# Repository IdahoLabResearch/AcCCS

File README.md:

# AcCCS
Access Capabilities for CCS (AcCCS - pronounced "access" /ˈakˌses/) provides a flexible and inexpensive solution to enable communications testing of various Electric Vehicle (EV) technologies that use the CCS charging standard(s).  This codebase is an example of tools and scripts capable of communicating with and emulating an Electric Vehicle Communications Controller (EVCC) and/or a Supply Equipment Communications Controller (SECC).

This project is the result of our efforts to find COTS hardware and existing open source software capable of communicating via HomePlug GreenPHY (HPGP) with CCS enabled vehicles and charging stations.  We are providing some basic scripts to emulate an EV (see [run_evcc.py](run_evcc.py)) or an EVSE (see [run_secc.py](run_secc.py)).  These two scripts utilize a third-party open source project that provide Scapy packet definitions for Layer 2 (HPGP - [layerscapy](https://github.com/FlUxIuS/HomePlugPWN/tree/master/layerscapy)). Our goal was to establish a persistent network connection with a target device so that we can test the device for network vulnerabilities.

To enable some testing of the IPv6 endpoints, the emulator scripts provide the ability to perform some basic port scans of the target.  This functionality is available using command-line options of the emulator.  The emulators can be further enhanced for additional port scanning activities or even fuzz testing of the selected CCS protocol.

> **Note:** This code was primarily developed and tested using the old DIN 70121 specification and schema.

A description of the [CurrentImplementation](/docs/CurrentImplementation.md) of our AcCCS box, as well as some supporting presentations, are found in the [docs](/docs/) folder.

**A final word:** All of this code was generated in our lab using extensive trial and error while monitoring communications between a couple EV and EVSE.  It has not been extensively tested with many vehicles or charging stations.  It was not written using formal software development and design methods.  We were just happy when it worked.  It is not pretty.

## Getting Started

For the full fresh-clone walkthrough — submodule clone, Python dependencies,
PKI certificates, the virtual veth pair, and a smoke test — see
[Project Setup](#project-setup).

## Hardware Configuration

Details regarding our current implementation and hardware configuration is found in the '''docs''' folder.

The ```resources``` directory includes the schematics and design files to create the PWM board used to emulate the SECC.  The following shows how all of the hardware is currently setup in the AcCCS boxes.

EVSE DEVOLO: [EVSE side configured dLAN Green Phy Eval Board](https://www.codico.com/en/evse-side-configured-dlan-green-phy-eval-board)\
PEV DEVOLO: [PEV side configured dLAN Green Phy Eval Board](https://www.codico.com/en/pev-side-configured-dlan-green-phy-eval-board)\
RASPBERRY PI: [Raspberry Pi 4 Model B](https://www.raspberrypi.com/products/raspberry-pi-4-model-b/)\
12V OUT: [12V Isolated DC/DC Converter](https://www.digikey.com/en/products/detail/cui-inc./PYBE30-Q24-S12-T/9859982)\
5V OUT: [5V Isolated DC/DC Converter](https://www.digikey.com/en/products/detail/cui-inc/PYBE30-Q24-S5-T/9859981)\
ETH: [USB to RJ45 Adapter](https://www.amazon.com/Gigabit-Adapter-CableCreation-Network-Supporting/dp/B07CKQY8HN)\
PWM PCB: [PWM PCB](resources/PWM_PCB/)

The devices labeled ETH, RELAY, 5V OUT, 12V OUT, and RASPBERRY PI are generic devices so a specific brand is not required. Nevertheless, the above links provided are the exact version of these devices we used in our AcCCS box. A brief description of each of these devices are as follows so that any devices that fits this description can probably be used with little to no alteration. Extra notes regarding the implementation and role of each device are also included.

**RASPBERRY PI:** For this project a raspberry pi was used, but any computer or microcontroller can be used in its place. A pi was used for its small form factor, I2C interface, and ability to run an OS. Whatever device is used for this role must support the following features: IPv4 and IPv6 networking, I2C interface (PWM board), 3 RJ-45 ports or the ability to connect RJ-45 adapters, and python support (unless you don't want to use the scripts provided in this project).

**PWM PCB and RELAYS:** The PWM circuit includes several on-board relays. The first two channels of the relay are used to emulate the J1772 states of a PEV. The J1772 signaling circuit below shows the resistance values used (found in the vehicle controller portion labeled R3 and R2). The next 2 channels are used to connect and disconnect the control pilot and proximity pilot lines for the EVSE emulation to mimic plugging and unplugging the charging cable. When connected, the control pilot line goes directly to the output and the proximity pilot ties a resistance to ground in accordance to the J1772 standard (R6 in the EVSE connector of the signaling circuit).

**12V/5V OUT:** These DC/DC power converters were used as a means to get +12V,-12V, and +5V power supplies, so they are not necessary if you have a way to supply these voltages by other means. If the provided configuration is used, the converters must be **ISOLATED** DC/DC converters so that you can tie the positive terminal of one 12V supply to the negative terminal of the other in order to create a -12V supply.

**ETH:** Any generic USB to RJ-45 adapter can be used. This is needed so that the Raspberry pi can interface with the two GreenPHY eval board radios via ethernet. Not necessary if your choice of controller has 3 RJ-45 ports.

**EVSE/PEV DEVOLO:** The GreenPHY eval board used acts as a radio that bridges ethernet communications over cat cable to HomePlug GreenPHY communications over a single signal wire and ground. These boards also automatically complete some of the level 2 HomePlug protocol specific actions, such as forming ALVNs according to the standard, so to work properly must be configured properly. Currently, these radios are purchased pre-configured from the vendor, but there may be some way to flash an unconfigured board with the contents of a configured board. There are also some jumper options present on the eval boards which should be configured so that the HomePlug GreenPHY is output over the two-wire terminal instead of coax.

The circuit shown below is what is used to generate the +12V to -12V 1kHz 5% Duty Cycle PWM signal that is supplied by the EVSE controller. It uses the TLC555CP chip to first generate a +12V to 0V 1kHz 5% Duty Cycle PWM. Other timer ICs could probably be used, but this is what worked for me. The output PWM's frequency and duty cycle are dependant on the values of two resistors and one capacitor (the 1.5k and 25k Ohm resistors and the 47 nanoFarad capacitor). In practice, the values of these components varied enough for the resulting signal to not fit within tolerances for the EVCC to recognize it as a 1kHz 5% PWM. So, in place of a 1.5k resistance a 10k potentiometer was used and in place of a 25k resistance a 22k resistor in series with a 10k potentiometer was used. In this configuration, the output of the 555 timer was probed with an oscilloscope and the potentiometers were tuned until the PWM was as close to the spec as possible. Next, the signal along with -12V DC is input into an Op-Amp so that the resulting output will be the required +12V to -12V PWM. In practice, the resulting PWM is closer to an +11V peak than +12V, so to compensate the resistor in series with the output was changed to a lower value (from a 1k Ohm to a 680 Ohm resistor). This is done so that when the PEV changes its internal resistances and changes the J1772 states, the resulting voltages are closer to the +9V and +6V peaks required by the standard.

555 Timer: [TLC555CP](https://www.digikey.com/en/products/detail/texas-instruments/TLC555CP/277502)\
Op-Amp: [LM6132BIN/NOPB](https://www.ti.com/product/LM6132/part-details/LM6132BIN/NOPB)

## Software Configuration

The DIN and ISO standards define that the TCP/IP communication between EVCC and SECC equipment use IPv6 networking with link-local addressing. For this reason, to properly communicate to these devices from a controller, IPv6 networking on the controller must be configured for link-local addressing on the interfaces that connect to the GreenPHY eval board radios.

### Python Module Dependencies
* scapy
* smbus
* expy

**Scapy** is used for all of the packet activities such as crafting, manipulation, sending, and receiving packets. 

**Smbus** is used for I2C communications with the PCB to operate the relays found on the PWM PCB.

**EXPy** is the Python binding over LF Energy EVerest's `libcbv2g` used for EXI
encode/decode (see [ADR-0002](docs/adr/0002-expy-codec-replacement.md)). EXPy is
installed from source and builds a C/C++ extension during `pip install`, which
adds the following install-time prerequisites on every target (dev machine and
Raspberry Pi alike):

* **CMake** ≥ 3.20
* **Ninja** ≥ 1.10
* A C/C++ toolchain (gcc/clang and the matching standard libraries)

Install these *before* `pip install` — [Project Setup](#project-setup) step 2
covers the Debian / Raspberry Pi OS one-liner.

### EVSE and EV Python Scripts
Below is a brief description of the entry-point scripts in this project. These scripts are provided as examples of how you might utilize this hardware in your own testing environment. This is not intended to be a finished product with all desired functionality. Some functionality is still a work in progress.

**run_secc.py:** Emulates an EVSE (SECC). When the AcCCS's EVSE CP and SIG GND are connected to the PEV's CP and GND, the script follows the J1772 spec by going through layer 2 HomePlug GreenPHY SLAC negotiations, layer 3 UDP SECC Discovery Protocol, and then layer 3 TCP/IPv6 communications. DIN SPEC 70121, ISO 15118-2, and ISO 15118-20 (AC and DC) are all supported, including TLS sessions, Plug & Charge, and bidirectional power transfer; which one a run speaks is chosen by the personality's `capabilities.supported_protocols` (see [Running the emulators](#running-the-emulators)).

**run_evcc.py:** Same as run_secc.py but for the EV side (EVCC); AcCCS's PEV CP and SIG GND should be connected to the EVSE's CP and GND pins.

A man-in-the-middle mode — two simultaneous connections to a PEV and an EVSE with packets forwarded (and optionally modified) between them — remains unimplemented. A simple bridge between the two is not workable because of the high cross-talk between CP lines, and the signalling is very susceptible to RF interference.

### Hardware bench tools

These helper scripts drive the I2C relay board directly, without loading a personality or opening a V2G session. They run only on the hardware host (the Pi, with the relay board on I2C bus 1); off the hardware — no `smbus`, no bus, or no permission on `/dev/i2c-1` — each exits with a one-line explanation rather than a traceback.

**scripts/evcc_relays.py:** Interactive control of the EV side's control-pilot relays for exercising the CP/PP wiring in isolation. Type a J1772 state (`a`/`b`/`c`) and watch the EVSE react; the relays are always opened again on exit. Like the emulator it touches only the EV side's pins, so a SECC running on the same box keeps its relays.

**scripts/reset_relays.py:** Turns *every* relay off in one deliberate whole-register write, regardless of which role set the bits. This recovers a board whose relays a hard-killed emulator left latched closed — the one case the per-role writes cannot clean up, since the owner is no longer around to clear them. It is the single sanctioned exception to the role-ownership rule (see [ADR-0007](docs/adr/0007-role-scoped-relay-ownership.md)); the pin-direction configuration is left untouched. **Do not run it while an emulator is live** — the same broad write that recovers an orphaned board will clear a healthy session's relays out from under it. It reports whether it cleared anything or found the board already off.

## Project Setup

This is the single, linear path from a fresh clone to a green virtual demo
session. Follow it top to bottom — each step is a prerequisite for the smoke
test at the end. The deeper reference sections below are linked from each step.

### 1. Clone with submodules

AcCCS vendors its third-party Layer 2 (HPGP) libraries as git submodules, so a
plain `git clone` is not enough:

```bash
git clone --recurse-submodules <clone-url>
cd AcCCS
git submodule sync
```

If git errors about locating specific repository versions, this usually
unsticks it:

```bash
git submodule update --force --recursive --init --remote
```

### 2. Python environment + dependencies

Use Python 3.10+ in an isolated environment — a `conda` env or a `venv` both
work. The pinned dependencies live in [`requirements.txt`](requirements.txt):

```bash
# conda
conda create -n AcCCS python=3.11 && conda activate AcCCS
# — or — venv
python -m venv .venv && source .venv/bin/activate

pip install -r requirements.txt
```

One dependency, **EXPy**, builds a C/C++ extension at install time (see
[ADR-0002](docs/adr/0002-expy-codec-replacement.md)), so a build toolchain
must be present *before* `pip install`. On Debian / Raspberry Pi OS:

```bash
sudo apt install cmake ninja-build build-essential
```

See [Software Configuration](#software-configuration) for the full dependency
rundown.

### 3. Generate PKI certificates

The stock personalities ship with TLS enabled (`tls.use_tls: true`,
`tls.enable_tls_1_3: true`), so the SECC needs a server certificate chain
before it can complete SDP/TLS. Generate it from the repo root:

```bash
bash app/shared/pki/create_certs.sh -v iso-2
```

Skipping this step is the most common first-run failure — it surfaces as
`FileNotFoundError: oemRootCACert.pem` followed by a cascading
`'TCPServer' object has no attribute 'ipv6_address_host'` traceback.

If you intend to run ISO 15118-20 scenarios, also generate the `-v iso-20`
chain:

```bash
bash app/shared/pki/create_certs.sh -v iso-20
```

See [Certificate Management](#certificate-management) for the Plug-and-Charge
context.

### 4. Create the virtual veth pair

The `--virtual` demo runs both emulators on one host over a veth pair
(`acccs_secc ↔ acccs_evcc`, with link-local addresses `fe80::1` / `fe80::2`).
Create it with:

```bash
sudo ./setup_veth.sh
```

This is also a prerequisite for the conformance tests.

### 5. Smoke test

With steps 1–4 done, run the stock SECC and EVCC in two terminals. The
emulators bind raw sockets, so they need root (`sudo`) or the `cap_net_raw`
capability.

Note the `sudo "$(which python)"` form: `sudo` resets `PATH` to its
`secure_path`, so a plain `sudo python` runs the *system* interpreter, which
lacks the dependencies you installed into the conda/venv environment from
step 2 (you'd hit `ModuleNotFoundError: No module named 'nmap'`). The
command substitution resolves to the activated environment's interpreter
*before* `sudo` runs, so the env's Python is used:

```bash
# Terminal 1
sudo "$(which python)" run_secc.py --config default-secc --virtual

# Terminal 2 (a second or two later)
sudo "$(which python)" run_evcc.py --config default-evcc --virtual
```

A clean session walks through these milestones:

```
SLAC → SDP/TLS → SessionSetup → ServiceDiscovery → PowerDelivery →
CurrentDemand loop → PowerDelivery → WeldingDetection → SessionStop
```

ending with the EVCC logging `Going to state A`. If you see that, your setup is
complete. See [Running the emulators](#running-the-emulators) for personality
and CLI-override details.

## Running the emulators

> **New here?** Complete [Project Setup](#project-setup) first — it covers the
> submodule clone, dependencies, PKI certificates, and the veth pair that the
> commands below assume are already in place.

Only two scripts are expected to be run from command line: ```run_evcc.py``` and ```run_secc.py```. The other scripts and files serve as tools and utilities for these scripts to run.

Both scripts take an optional `--config <personality.yaml>` flag and an
optional `--runtime <runtime.yaml>`. When `--config` is omitted, each
script defaults to its per-role DIN device file (`run_secc.py` →
`din_dc_extended-secc`, `run_evcc.py` → `din_dc_extended-evcc`). Stock personalities live in the
[`personalities/`](personalities/) directory; the bundled defaults are a
complete materialised dump of every field with its built-in value:

The emulators bind raw sockets, so they need root (`sudo`) or the
`cap_net_raw` capability. Use the `sudo "$(which python)"` form so the
activated environment's interpreter is used — a plain `sudo python` resets
`PATH` to `secure_path` and runs the *system* interpreter, which lacks your
installed dependencies (see [Project Setup → Smoke test](#5-smoke-test) for
the full explanation):

```bash
# Run the stock virtual SECC and EVCC over the acccs_secc/acccs_evcc veth pair
sudo ./setup_veth.sh
sudo "$(which python)" run_secc.py --config default-secc --virtual
sudo "$(which python)" run_evcc.py --config default-evcc --virtual
```

Personality search order (per [ADR-0001](docs/adr/0001-personality-yaml-config.md)):

1. explicit `--config <path>` (file path);
2. `personalities/<name>.yaml` in the repo;
3. `~/.acccs/personalities/<name>.yaml` (user-local).

### CLI overrides

Personality fields are **not** CLI-overridable — they describe *who* the
emulated device is, and changing them mid-experiment is a different
personality. Operational knobs are overridable:

| Flag | Overrides |
|---|---|
| `--log-level <LEVEL>` | `runtime.log.console_level` |
| `--file-log-level <LEVEL>` | `runtime.log.file_level` |
| `--virtual` | `runtime.virtual` |
| `--nmap` | `runtime.nmap.enabled` |
| `--nmap-args <ARGS>` | `runtime.nmap.args` |
| `--nmap-ports <SPEC>` | `runtime.nmap.ports` |
| `--source-port <PORT>` | `runtime.source_port` |
| `--modified-cordset` | `runtime.modified_cordset` (SECC only) |

To customise a personality, copy `personalities/default-<role>.yaml` to a
new file and edit. The Pydantic loader validates strictly — unknown keys
are a hard error. See [`docs/personality-authoring.md`](docs/personality-authoring.md)
for a section-by-section authoring guide and the bundled example library.

## Certificate Management

Basic TLS certificate generation for the demo is covered in
[Project Setup](#project-setup) step 3. This section provides the deeper
Plug-and-Charge context and the contract-certificate workflow.

### Plug and Charge (ISO 15118-2 and ISO 15118-20)
For Plug and Charge, certificates and private keys have to be created at the beginning. Go to the [pki](/app/shared/pki) directory and run the ```create_certs.sh``` script like this:
```bash
./create_certs.sh -v iso-2
```
or
```bash
./create_certs.sh -v iso-20
```
If you are running it for the first time, you may have to change the permission to be able to exceute it. In this case, do this:
```bash
chmod 755 create_certs.sh
```

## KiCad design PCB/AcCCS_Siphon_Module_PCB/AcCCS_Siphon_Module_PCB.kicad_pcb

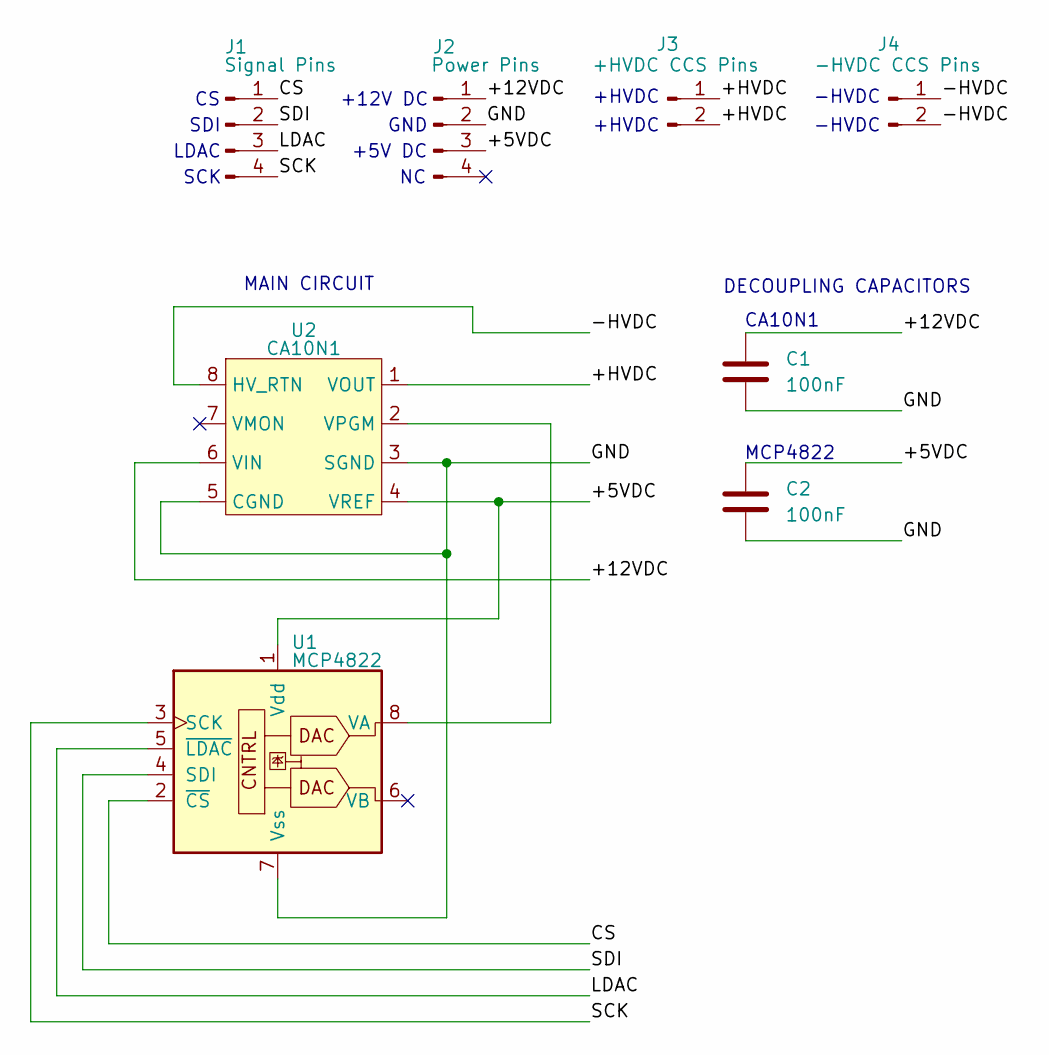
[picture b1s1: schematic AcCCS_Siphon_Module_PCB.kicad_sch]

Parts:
C1, C2: 100nF; C_Disc_D7.5mm_W5.0mm_P5.00mm
J1: Signal Pins; PinSocket_1x04_P2.54mm_Vertical
J2: Power Pins; PinSocket_1x04_P2.54mm_Vertical
J3: +HVDC CCS Pins; TerminalBlock_Phoenix_MKDS-1,5-2_1x02_P5.00mm_Horizontal
J4: -HVDC CCS Pins; TerminalBlock_Phoenix_MKDS-1,5-2_1x02_P5.00mm_Horizontal
U1: MCP4822; DIP-8_W7.62mm
U2: CA10N1; CA10N

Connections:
/+5VDC: C2.1, J2.3, U1.1 (Vdd), U2.4 (VREF)
/+12VDC: C1.1, J2.1, U2.6 (VIN)
/+HVDC: J3.1, J3.2, U2.1 (VOUT)
/-HVDC: J4.1, J4.2, U2.8 (HV_RTN)
/CS: J1.1, U1.2 (~CS)
/GND: C1.2, C2.2, J2.2, U1.7 (Vss), U2.3 (SGND), U2.5 (CGND)
/LDAC: J1.3, U1.5 (~LDAC)
/SCK: J1.4, U1.3 (SCK)
/SDI: J1.2, U1.4 (SDI)
unnamed: U1.8 (VA), U2.2 (VPGM)

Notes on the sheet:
+5V DC
MAIN CIRCUIT
+12V DC
-HVDC
+HVDC
DECOUPLING CAPACITORS
SCK
LDAC
GND
MCP4822
CA10N1
SDI

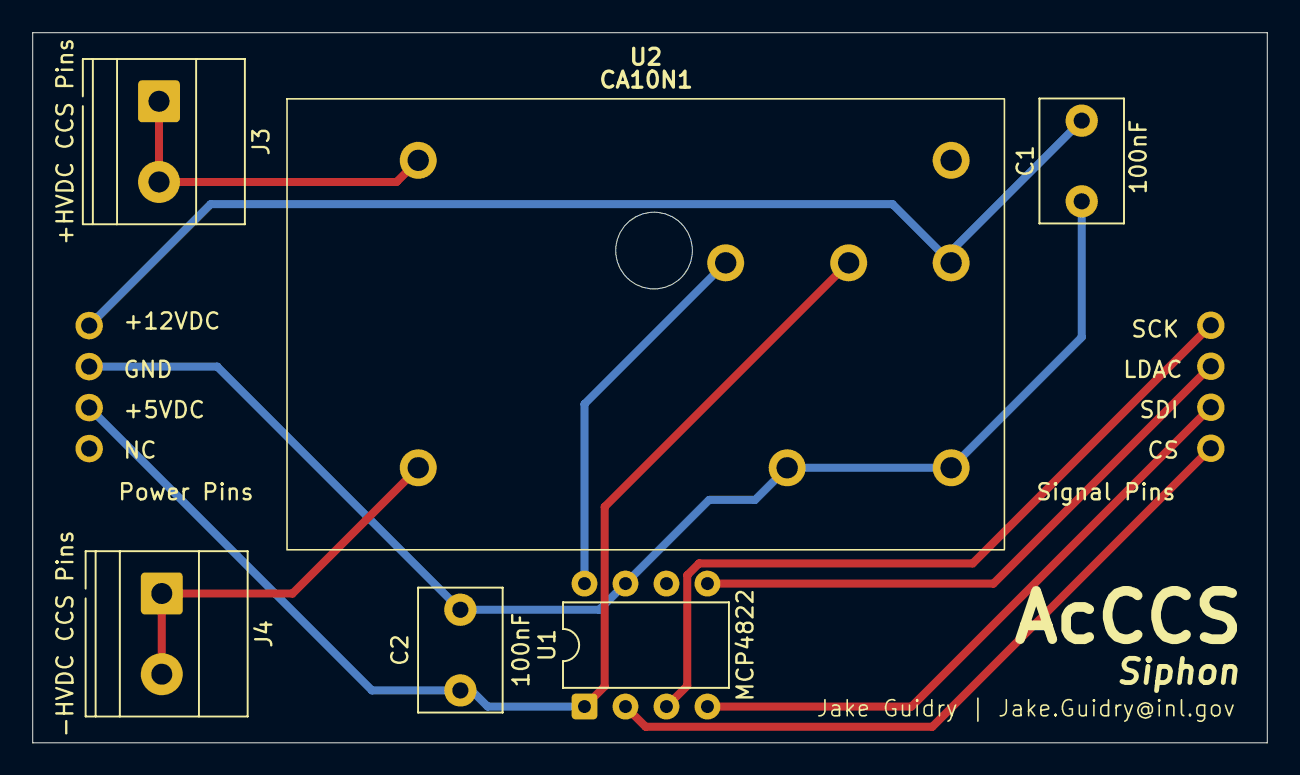
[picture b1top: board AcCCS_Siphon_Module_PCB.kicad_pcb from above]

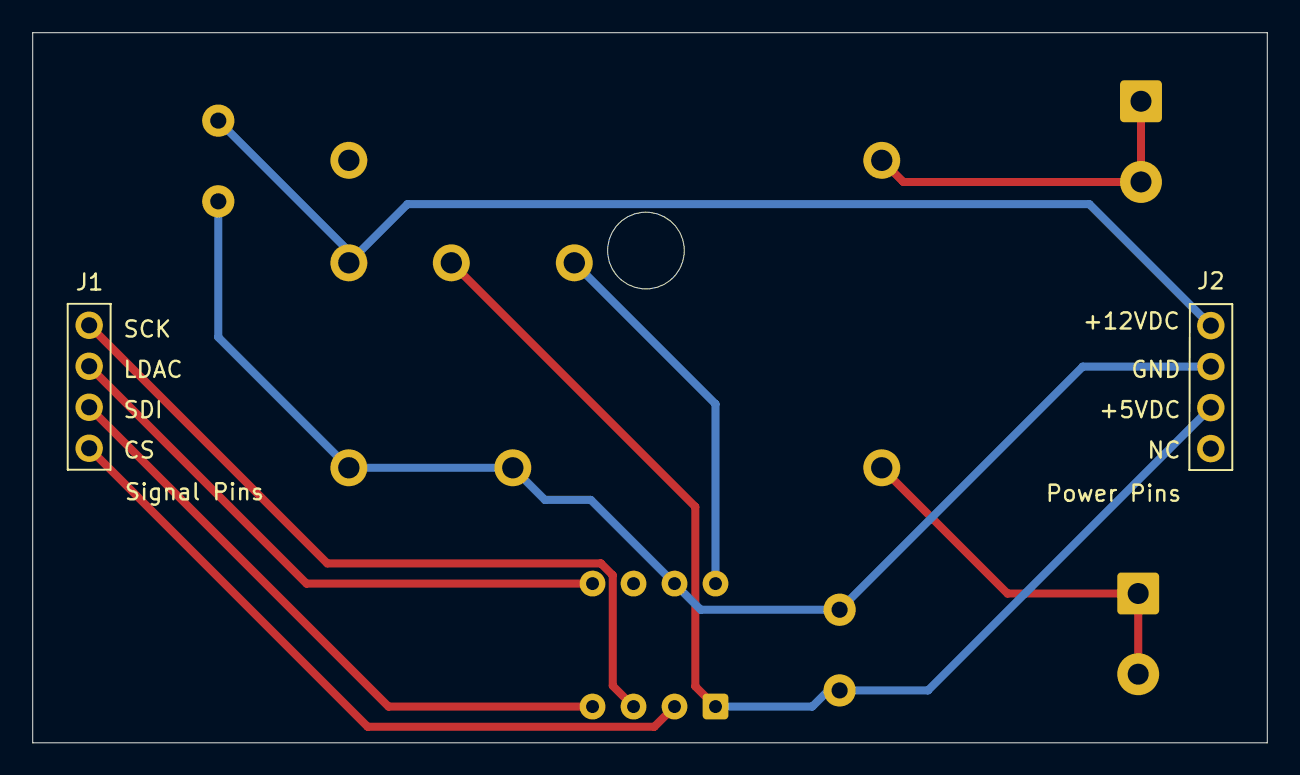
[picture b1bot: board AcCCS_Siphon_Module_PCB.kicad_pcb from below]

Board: 2 copper layers, 76.5 x 44.0 mm, 8 parts (2 on the bottom side), 10 nets.

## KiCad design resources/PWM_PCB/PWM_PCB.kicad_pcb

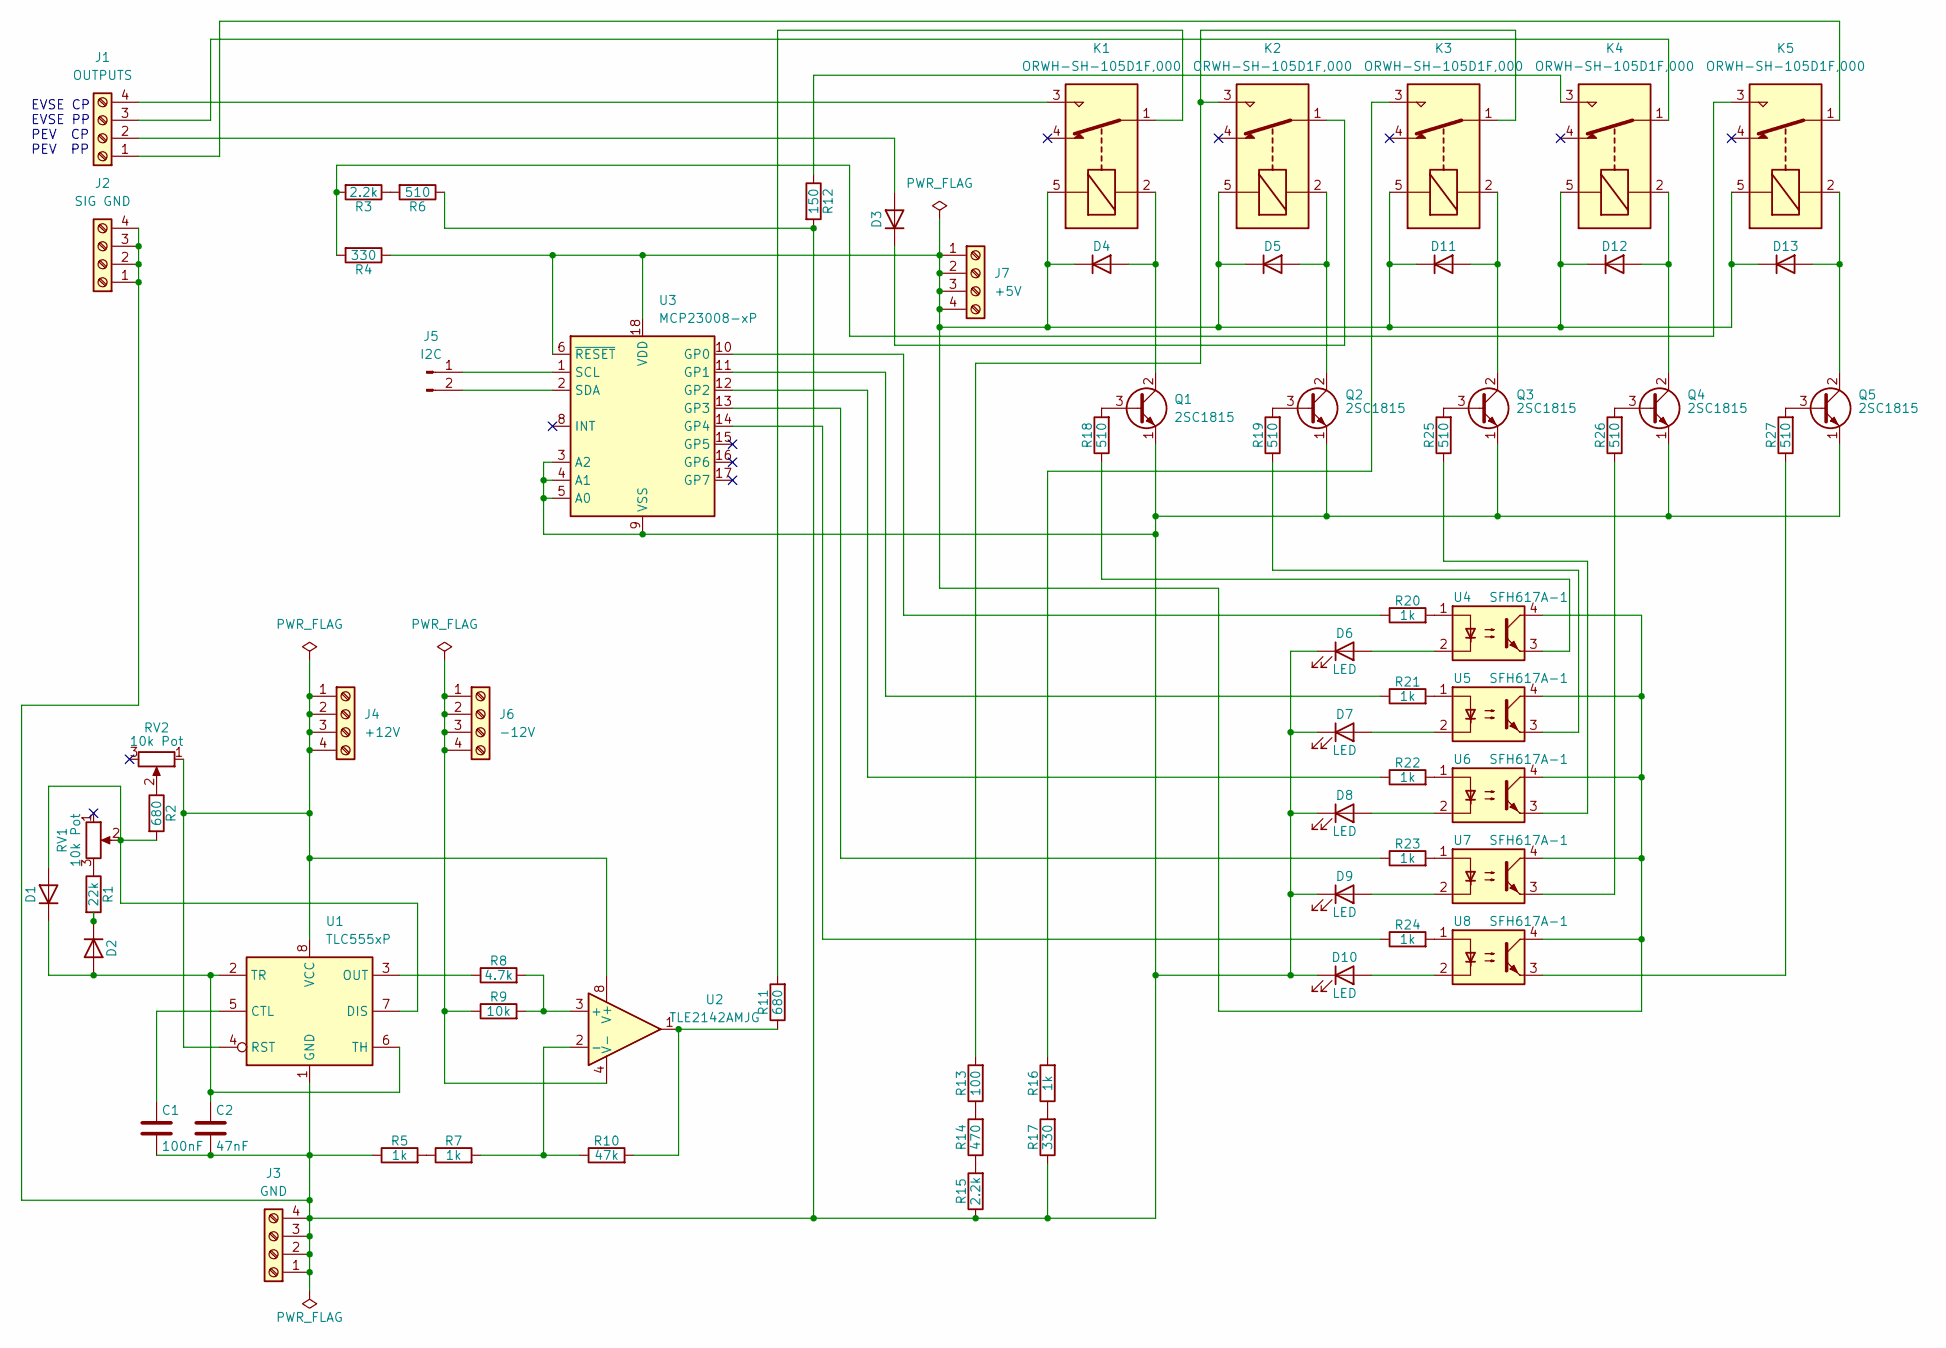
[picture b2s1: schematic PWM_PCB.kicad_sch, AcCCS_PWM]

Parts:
C1: 100nF; C_Disc_D7.5mm_W5.0mm_P5.00mm
C2: 47nF; C_Disc_D7.5mm_W5.0mm_P5.00mm
D1, D2, D3, D4, D5, D11, D12, D13: D_A-405_P7.62mm_Horizontal
D6, D7, D8, D9, D10: LED; LED_D1.8mm_W3.3mm_H2.4mm
J1: OUTPUTS; TerminalBlock_Phoenix_MKDS-1,5-4_1x04_P5.00mm_Horizontal
J2: SIG GND; TerminalBlock_Phoenix_MKDS-1,5-4_1x04_P5.00mm_Horizontal
J3: GND; TerminalBlock_Phoenix_MKDS-1,5-4_1x04_P5.00mm_Horizontal
J4: +12V; TerminalBlock_Phoenix_MKDS-1,5-4_1x04_P5.00mm_Horizontal
J5: I2C; PinHeader_1x02_P2.54mm_Vertical
J6: -12V; TerminalBlock_Phoenix_MKDS-1,5-4_1x04_P5.00mm_Horizontal
J7: +5V; TerminalBlock_Phoenix_MKDS-1,5-4_1x04_P5.00mm_Horizontal
K1, K2, K3, K4, K5: ORWH-SH-105D1F,000; Relay_SPDT_SANYOU_SRD_Series_Form_C
Q1, Q2, Q3, Q4, Q5: 2SC1815; TO-92_Inline
R1: 22k; R_Axial_DIN0207_L6.3mm_D2.5mm_P7.62mm_Horizontal
R2, R11: 680; R_Axial_DIN0207_L6.3mm_D2.5mm_P7.62mm_Horizontal
R3, R15: 2.2k; R_Axial_DIN0207_L6.3mm_D2.5mm_P7.62mm_Horizontal
R4, R17: 330; R_Axial_DIN0207_L6.3mm_D2.5mm_P7.62mm_Horizontal
R5, R7, R16, R20, R21, R22, R23, R24: 1k; R_Axial_DIN0207_L6.3mm_D2.5mm_P7.62mm_Horizontal
R6, R18, R19, R25, R26, R27: 510; R_Axial_DIN0207_L6.3mm_D2.5mm_P7.62mm_Horizontal
R8: 4.7k; R_Axial_DIN0207_L6.3mm_D2.5mm_P7.62mm_Horizontal
R9: 10k; R_Axial_DIN0207_L6.3mm_D2.5mm_P7.62mm_Horizontal
R10: 47k; R_Axial_DIN0207_L6.3mm_D2.5mm_P7.62mm_Horizontal
R12: 150; R_Axial_DIN0207_L6.3mm_D2.5mm_P7.62mm_Horizontal
R13: 100; R_Axial_DIN0207_L6.3mm_D2.5mm_P7.62mm_Horizontal
R14: 470; R_Axial_DIN0207_L6.3mm_D2.5mm_P7.62mm_Horizontal
RV1, RV2: 10k Pot; 10K_TrimPot
U1: TLC555xP; DIP-8_W7.62mm
U2: TLE2142AMJG; DIP-8_W7.62mm
U3: MCP23008-xP; DIP-18_W7.62mm
U4, U5, U6, U7, U8: SFH617A-1; DIP-4_W7.62mm

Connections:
unnamed: D1.2 (A), R2.2, RV1.2, U1.7 (DIS)
unnamed: C2.1, D1.1 (K), D2.2 (A), U1.2 (TR), U1.6 (TH)
unnamed: D2.1 (K), R1.2
unnamed: D3.2 (A), J1.2
unnamed: D3.1 (K), K2.1
unnamed: D4.2 (A), K1.2, Q1.2 (C)
unnamed: D5.2 (A), K2.2, Q2.2 (C)
unnamed: D6.2 (A), U4.2
unnamed: D7.2 (A), U5.2
unnamed: D8.2 (A), U6.2
unnamed: D9.2 (A), U7.2
unnamed: D10.2 (A), U8.2
unnamed: C1.2, C2.2, D6.1 (K), D7.1 (K), D8.1 (K), D9.1 (K), D10.1 (K), J2.1, J2.2, J2.3, J2.4, J3.1, J3.2, J3.3, J3.4, Q1.1 (E), Q2.1 (E), Q3.1 (E), Q4.1 (E), Q5.1 (E), R5.1, R6.1, R12.2, R15.1, R17.1, U1.1 (GND), U3.3 (A2), U3.4 (A1), U3.5 (A0), U3.9 (VSS)
unnamed: D11.2 (A), K3.2, Q3.2 (C)
unnamed: D4.1 (K), D5.1 (K), D11.1 (K), D12.1 (K), D13.1 (K), J7.1, J7.2, J7.3, J7.4, K1.5, K2.5, K3.5, K4.5, K5.5, R4.1, U3.6 (~RESET), U3.18 (VDD), U4.4, U5.4, U6.4, U7.4, U8.4
unnamed: D12.2 (A), K4.2, Q4.2 (C)
unnamed: D13.2 (A), K5.2, Q5.2 (C)
unnamed: J1.1, K5.1
unnamed: J1.3, K4.1
unnamed: J1.4, K1.3
unnamed: J4.1, J4.2, J4.3, J4.4, RV2.1, U1.4 (RST), U1.8 (VCC), U2.8 (V+)
unnamed: J5.1, U3.1 (SCL)
unnamed: J5.2, U3.2 (SDA)
unnamed: J6.1, J6.2, J6.3, J6.4, R9.1, U2.4 (V-)
unnamed: K1.1, R11.2
unnamed: K2.3, K3.1, R13.2
unnamed: K3.3, R16.2
unnamed: K4.3, R12.1
unnamed: K5.3, R3.2, R4.2
unnamed: Q1.3 (B), R18.2
unnamed: Q2.3 (B), R19.2
unnamed: Q3.3 (B), R25.2
unnamed: Q4.3 (B), R26.2
unnamed: Q5.3 (B), R27.2
unnamed: R1.1, RV1.3
unnamed: R2.1, RV2.2
unnamed: R3.1, R6.2
unnamed: R5.2, R7.1
unnamed: R10.2, R11.1, U2.1
unnamed: R13.1, R14.2
unnamed: R14.1, R15.2
unnamed: R16.1, R17.2
unnamed: R18.1, U4.3
unnamed: R19.1, U5.3
unnamed: R20.2, U4.1
unnamed: R21.2, U5.1
unnamed: R22.2, U6.1
unnamed: R23.2, U7.1
unnamed: R24.2, U8.1
unnamed: R25.1, U6.3
unnamed: R26.1, U7.3
unnamed: R27.1, U8.3
unnamed: C1.1, U1.5 (CTL)
unnamed: R8.1, U1.3 (OUT)
unnamed: R8.2, R9.2, U2.3 (+)
unnamed: R7.2, R10.1, U2.2 (-)
unnamed: R20.1, U3.10 (GP0)
unnamed: R21.1, U3.11 (GP1)
unnamed: R22.1, U3.12 (GP2)
unnamed: R23.1, U3.13 (GP3)
unnamed: R24.1, U3.14 (GP4)

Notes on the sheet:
EVSE CP EVSE PP PEV CP PEV PP

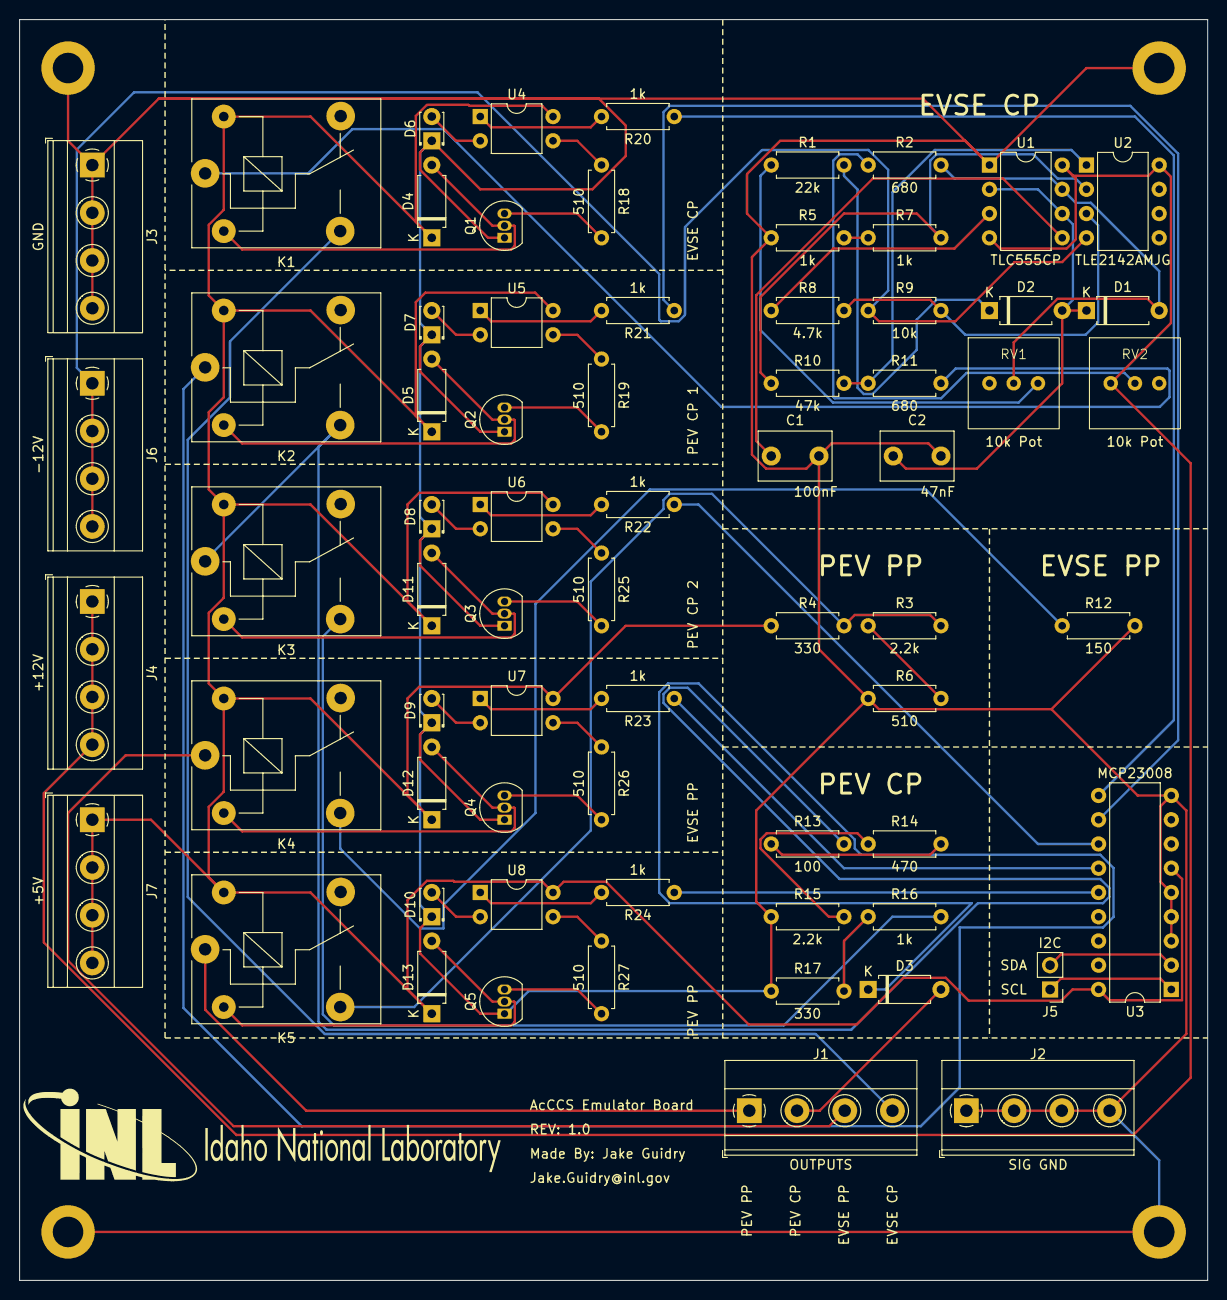
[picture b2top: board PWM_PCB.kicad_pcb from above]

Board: 2 copper layers, 124.5 x 132.1 mm, 69 parts (0 on the bottom side), 61 nets.

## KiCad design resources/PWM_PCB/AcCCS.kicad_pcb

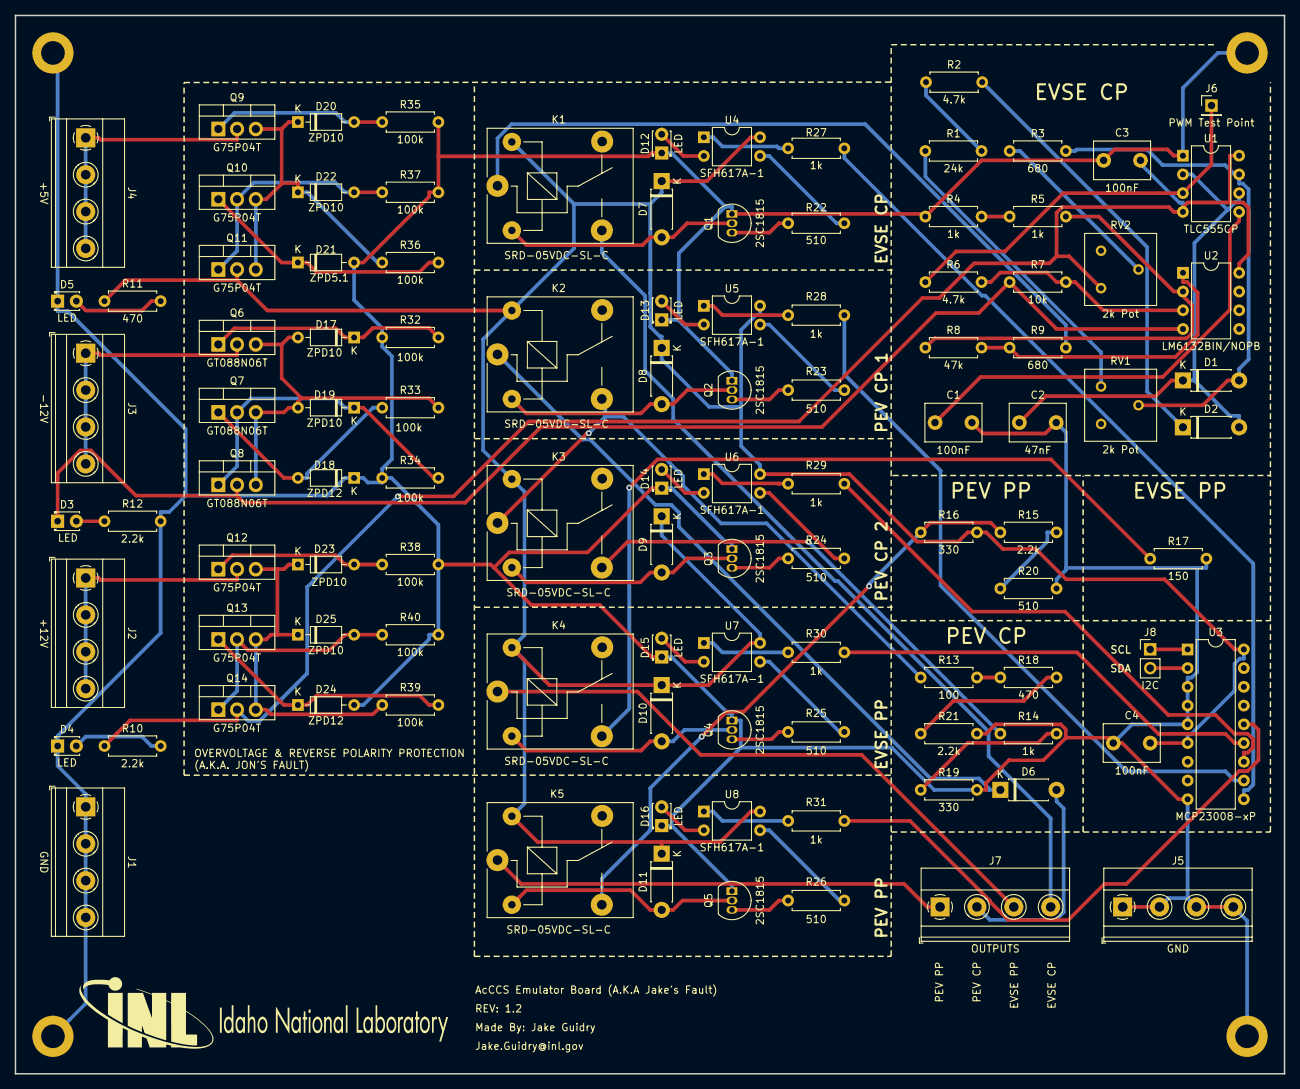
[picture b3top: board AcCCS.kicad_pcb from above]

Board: 2 copper layers, 172.1 x 143.5 mm, 110 parts (0 on the bottom side), 80 nets.

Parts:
C1, C3, C4: 100nF; C_Disc_D7.5mm_W5.0mm_P5.00mm
C2: 47nF; C_Disc_D7.5mm_W5.0mm_P5.00mm
D1, D2, D7, D8, D9, D10, D11: D_DO-41_SOD81_P7.62mm_Horizontal
D3, D4, D5, D12, D13, D14, D15, D16: LED; LED_D1.8mm_W3.3mm_H2.4mm
D6: D; D_DO-41_SOD81_P7.62mm_Horizontal
D17, D19, D20, D22, D23, D25: ZPD10; D_DO-35_SOD27_P7.62mm_Horizontal
D18, D24: ZPD12; D_DO-35_SOD27_P7.62mm_Horizontal
D21: ZPD5.1; D_DO-35_SOD27_P7.62mm_Horizontal
J1, J5: GND; TerminalBlock_Phoenix_MKDS-1,5-4_1x04_P5.00mm_Horizontal
J2: +12V; TerminalBlock_Phoenix_MKDS-1,5-4_1x04_P5.00mm_Horizontal
J3: -12V; TerminalBlock_Phoenix_MKDS-1,5-4_1x04_P5.00mm_Horizontal
J4: +5V; TerminalBlock_Phoenix_MKDS-1,5-4_1x04_P5.00mm_Horizontal
J6: PWM Test Point; PinHeader_1x01_P2.54mm_Vertical
J7: OUTPUTS; TerminalBlock_Phoenix_MKDS-1,5-4_1x04_P5.00mm_Horizontal
J8: I2C; PinHeader_1x02_P2.54mm_Vertical
K1, K2, K3, K4, K5: SRD-05VDC-SL-C; Relay_SPDT_SANYOU_SRD_Series_Form_C
M1, M2, M3, M4: MountingHole_3.2mm_M3_DIN965_Pad
Q1, Q2, Q3, Q4, Q5: 2SC1815; TO-92_Inline
Q6, Q7, Q8: GT088N06T; TO-220-3_Vertical
Q9, Q10, Q11, Q12, Q13, Q14: G75P04T; TO-220-3_Vertical
R1: 24k; R_Axial_DIN0207_L6.3mm_D2.5mm_P7.62mm_Horizontal
R2, R6: 4.7k; R_Axial_DIN0207_L6.3mm_D2.5mm_P7.62mm_Horizontal
R3, R9: 680; R_Axial_DIN0207_L6.3mm_D2.5mm_P7.62mm_Horizontal
R4, R5, R14, R27, R28, R29, R30, R31: 1k; R_Axial_DIN0207_L6.3mm_D2.5mm_P7.62mm_Horizontal
R7: 10k; R_Axial_DIN0207_L6.3mm_D2.5mm_P7.62mm_Horizontal
R8: 47k; R_Axial_DIN0207_L6.3mm_D2.5mm_P7.62mm_Horizontal
R10, R12, R15, R21: 2.2k; R_Axial_DIN0207_L6.3mm_D2.5mm_P7.62mm_Horizontal
R11, R18: 470; R_Axial_DIN0207_L6.3mm_D2.5mm_P7.62mm_Horizontal
R13: 100; R_Axial_DIN0207_L6.3mm_D2.5mm_P7.62mm_Horizontal
R16, R19: 330; R_Axial_DIN0207_L6.3mm_D2.5mm_P7.62mm_Horizontal
R17: 150; R_Axial_DIN0207_L6.3mm_D2.5mm_P7.62mm_Horizontal
R20, R22, R23, R24, R25, R26: 510; R_Axial_DIN0207_L6.3mm_D2.5mm_P7.62mm_Horizontal
R32, R33, R34, R35, R36, R37, R38, R39, R40: 100k; R_Axial_DIN0207_L6.3mm_D2.5mm_P7.62mm_Horizontal
RV1, RV2: 2k Pot; Potentiometer_Bourns_3386F_Vertical
U1: TLC555CP; DIP-8_W7.62mm
U2: LM6132BIN/NOPB; DIP-8_W7.62mm
U3: MCP23008-xP; DIP-18_W7.62mm
U4, U5, U6, U7, U8: SFH617A-1; DIP-4_W7.62mm

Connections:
/555_OUT: J6.1, R6.1, U1.3 (OUT)
/+5V: C4.2, D7.1 (K), D8.1 (K), D9.1 (K), D10.1 (K), D11.1 (K), K1.5, K2.5, K3.5, K4.5, K5.5, Q11.2 (D), R11.1, R16.2, U3.6 (~RESET), U3.18 (VDD), U4.4, U5.4, U6.4, U7.4, U8.4
/+5V_IN: J4.1, J4.2, J4.3, J4.4, Q9.2 (D)
/+12V: C3.2, Q14.2 (D), R10.1, RV2.1, U1.4 (RST), U1.8 (VCC), U2.8 (V+)
/+12V_IN: J2.1, J2.2, J2.3, J2.4, Q12.2 (D)
/-12V: D3.1 (K), Q8.2 (D), R7.1, U2.4 (V-)
/-12V_IN: J3.1, J3.2, J3.3, J3.4, Q6.2 (D)
/EVSE_CP: J7.4, K1.3
/EVSE_PP: J7.3, K4.1
/GND: C1.2, C2.2, C3.1, C4.1, D4.1 (K), D5.1 (K), D12.1 (K), D13.1 (K), D14.1 (K), D15.1 (K), D16.1 (K), D18.1 (K), D21.2 (A), D24.2 (A), J1.1, J1.2, J1.3, J1.4, J5.1, J5.2, J5.3, J5.4, M1.1, M2.1, M3.1, M4.1, Q1.1 (E), Q2.1 (E), Q3.1 (E), Q4.1 (E), Q5.1 (E), R4.1, R12.2, R17.2, R19.2, R20.2, R21.2, R32.2, R34.2, R35.2, R37.2, R38.2, R40.2, U1.1 (GND), U3.3 (A2), U3.4 (A1), U3.5 (A0), U3.9 (VSS)
/GP0: R27.1, U3.10 (GP0)
/GP1: R28.1, U3.11 (GP1)
/GP2: R29.1, U3.12 (GP2)
/GP3: R30.1, U3.13 (GP3)
/GP4: R31.1, U3.14 (GP4)
/I2C_SCL: J8.1, U3.1 (SCL)
/I2C_SDA: J8.2, U3.2 (SDA)
/OPAMP_OUT: K1.1, R9.2
/PEV_CP: D6.2 (A), J7.2
/PEV_PP: J7.1, K5.1
unnamed: D1.2 (A), R3.2, RV1.2, U1.7 (DIS)
unnamed: C2.1, D1.1 (K), D2.2 (A), U1.2 (TR), U1.6 (TH)
unnamed: D2.1 (K), R2.2
unnamed: D3.2 (A), R12.1
unnamed: D4.2 (A), R10.2
unnamed: D5.2 (A), R11.2
unnamed: D6.1 (K), K2.1
unnamed: D7.2 (A), K1.2, Q1.2 (C)
unnamed: D8.2 (A), K2.2, Q2.2 (C)
unnamed: D9.2 (A), K3.2, Q3.2 (C)
unnamed: D10.2 (A), K4.2, Q4.2 (C)
unnamed: D11.2 (A), K5.2, Q5.2 (C)
unnamed: D12.2 (A), U4.2
unnamed: D13.2 (A), U5.2
unnamed: D14.2 (A), U6.2
unnamed: D15.2 (A), U7.2
unnamed: D16.2 (A), U8.2
unnamed: D17.2 (A), D19.2 (A), Q6.3 (S), Q7.3 (S), Q8.3 (S), R33.1
unnamed: D17.1 (K), Q6.1 (G), R32.1
unnamed: D18.2 (A), Q7.1 (G), R33.2
unnamed: D19.1 (K), Q7.2 (D), Q8.1 (G), R34.1
unnamed: D20.2 (A), Q9.1 (G), R35.1
unnamed: D20.1 (K), D22.1 (K), Q9.3 (S), Q10.3 (S), Q11.3 (S), R36.1
unnamed: D21.1 (K), Q10.1 (G), R36.2
unnamed: D22.2 (A), Q10.2 (D), Q11.1 (G), R37.1
unnamed: D23.2 (A), Q12.1 (G), R38.1
unnamed: D23.1 (K), D25.1 (K), Q12.3 (S), Q13.3 (S), Q14.3 (S), R39.1
unnamed: D24.1 (K), Q13.1 (G), R39.2
unnamed: D25.2 (A), Q13.2 (D), Q14.1 (G), R40.1
unnamed: K2.3, K3.1, R13.1
unnamed: K3.3, R14.1
unnamed: K4.3, R17.1
unnamed: K5.3, R15.1, R16.1
unnamed: Q1.3 (B), R22.2
unnamed: Q2.3 (B), R23.2
unnamed: Q3.3 (B), R24.2
unnamed: Q4.3 (B), R25.2
unnamed: Q5.3 (B), R26.2
unnamed: R1.1, RV1.3
unnamed: R1.2, R2.1
unnamed: R3.1, RV2.2
unnamed: R4.2, R5.1
unnamed: R8.2, R9.1, U2.1
unnamed: R13.2, R18.1
unnamed: R14.2, R19.1
unnamed: R15.2, R20.1
unnamed: R18.2, R21.1
unnamed: R22.1, U4.3
unnamed: R23.1, U5.3
unnamed: R24.1, U6.3
unnamed: R25.1, U7.3
unnamed: R26.1, U8.3
unnamed: R27.2, U4.1
unnamed: R28.2, U5.1
unnamed: R29.2, U6.1
unnamed: R30.2, U7.1
unnamed: R31.2, U8.1
unnamed: C1.1, U1.5 (CTL)
unnamed: R6.2, R7.2, U2.3 (+)
unnamed: R5.2, R8.1, U2.2 (-)

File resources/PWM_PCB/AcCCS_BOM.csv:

#,Reference,Qty,Value,Footprint,Website
1,"C1, C3, C4",3,100nF,Capacitor_THT:C_Disc_D7.5mm_W5.0mm_P5.00mm,https://www.digikey.com/en/products/detail/kemet/C322C104K5R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
2,C2,1,47nF,Capacitor_THT:C_Disc_D7.5mm_W5.0mm_P5.00mm,https://www.digikey.com/en/products/detail/kemet/C322C473K5R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
3,"D1, D2, D6, D7, D8, D9, D10, D11",8,~,Diode_THT:D_DO-41_SOD81_P7.62mm_Horizontal,https://www.digikey.com/en/products/detail/micro-commercial-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
4,"D3, D4, D5, D12, D13, D14, D15, D16",8,LED,LED_THT:LED_D1.8mm_W3.3mm_H2.4mm,https://www.digikey.com/en/products/detail/w%C3%BCrth-elektr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
5,"D17, D19, D20, D22, D23, D25",6,ZPD10,Diode_THT:D_DO-35_SOD27_P7.62mm_Horizontal,https://www.digikey.com/en/products/detail/diotec-semiconduc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
6,"D18, D24",2,ZPD12,Diode_THT:D_DO-35_SOD27_P7.62mm_Horizontal,https://www.digikey.com/en/products/detail/diotec-semiconduc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
7,D21,1,ZPD5.1,Diode_THT:D_DO-35_SOD27_P7.62mm_Horizontal,https://www.digikey.com/en/products/detail/diotec-semiconduc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
8,"J1, J5",2,GND,"TerminalBlock_Phoenix:TerminalBlock_Phoenix_MKDS-1,5-4_1x04_P5.00mm_Horizontal",https://www.digikey.com/en/products/detail/te-connectivity-a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
9,J2,1,+12V,"TerminalBlock_Phoenix:TerminalBlock_Phoenix_MKDS-1,5-4_1x04_P5.00mm_Horizontal",https://www.digikey.com/en/products/detail/te-connectivity-a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
10,J3,1,-12V,"TerminalBlock_Phoenix:TerminalBlock_Phoenix_MKDS-1,5-4_1x04_P5.00mm_Horizontal",https://www.digikey.com/en/products/detail/te-connectivity-a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
11,J4,1,+5V,"TerminalBlock_Phoenix:TerminalBlock_Phoenix_MKDS-1,5-4_1x04_P5.00mm_Horizontal",https://www.digikey.com/en/products/detail/te-connectivity-a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
12,J6,1,PWM Test Point,Connector_PinHeader_2.54mm:PinHeader_1x01_P2.54mm_Vertical,https://www.digikey.com/en/products/detail/sullins-connector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
13,J7,1,OUTPUTS,"TerminalBlock_Phoenix:TerminalBlock_Phoenix_MKDS-1,5-4_1x04_P5.00mm_Horizontal",https://www.digikey.com/en/products/detail/te-connectivity-a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
14,J8,1,I2C,Connector_PinHeader_2.54mm:PinHeader_1x02_P2.54mm_Vertical,https://www.digikey.com/en/products/detail/sullins-connector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
15,"K1, K2, K3, K4, K5",5,SRD-05VDC-SL-C,Relay_THT:Relay_SPDT_SANYOU_SRD_Series_Form_C,https://www.digikey.com/en/products/detail/amphenol-anytek/A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
16,"Q1, Q2, Q3, Q4, Q5",5,2SC1815,Package_TO_SOT_THT:TO-92_Inline,https://www.digikey.com/en/products/detail/central-semicondu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
17,"Q6, Q7, Q8",3,GT088N06T,Package_TO_SOT_THT:TO-220-3_Vertical,https://www.digikey.com/en/products/detail/goford-semiconduc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
18,"Q9, Q10, Q11, Q12, Q13, Q14",6,G75P04T,Package_TO_SOT_THT:TO-220-3_Vertical,https://www.digikey.com/en/products/detail/goford-semiconduc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
19,R1,1,24k,Resistor_THT:R_Axial_DIN0207_L6.3mm_D2.5mm_P7.62mm_Horizontal,https://www.amazon.com/gp/product/B07HDGJC2N
20,"R2, R6",2,4.7k,Resistor_THT:R_Axial_DIN0207_L6.3mm_D2.5mm_P7.62mm_Horizontal,https://www.amazon.com/gp/product/B07HDFHPP3
21,"R3, R9",2,680,Resistor_THT:R_Axial_DIN0207_L6.3mm_D2.5mm_P7.62mm_Horizontal,https://www.amazon.com/gp/product/B07HDFJVYF
22,"R4, R5, R14, R27, R28, R29, R30, R31",8,1k,Resistor_THT:R_Axial_DIN0207_L6.3mm_D2.5mm_P7.62mm_Horizontal,https://www.amazon.com/gp/product/B07HDDWFDD
23,R7,1,10k,Resistor_THT:R_Axial_DIN0207_L6.3mm_D2.5mm_P7.62mm_Horizontal,https://www.amazon.com/gp/product/B07HDGX5LM
24,R8,1,47k,Resistor_THT:R_Axial_DIN0207_L6.3mm_D2.5mm_P7.62mm_Horizontal,https://www.amazon.com/gp/product/B07HDFHVLL
25,"R10, R12, R15, R21",4,2.2k,Resistor_THT:R_Axial_DIN0207_L6.3mm_D2.5mm_P7.62mm_Horizontal,https://www.amazon.com/gp/product/B07HDFT8NF
26,"R11, R18",2,470,Resistor_THT:R_Axial_DIN0207_L6.3mm_D2.5mm_P7.62mm_Horizontal,https://www.amazon.com/gp/product/B07HDFBR2P
27,R13,1,100,Resistor_THT:R_Axial_DIN0207_L6.3mm_D2.5mm_P7.62mm_Horizontal,https://www.amazon.com/gp/product/B07QKDSCSM
28,"R16, R19",2,330,Resistor_THT:R_Axial_DIN0207_L6.3mm_D2.5mm_P7.62mm_Horizontal,https://www.amazon.com/gp/product/B07HDFFN81
29,R17,1,150,Resistor_THT:R_Axial_DIN0207_L6.3mm_D2.5mm_P7.62mm_Horizontal,https://www.amazon.com/gp/product/B07HDH2M4M
30,"R20, R22, R23, R24, R25, R26",6,510,Resistor_THT:R_Axial_DIN0207_L6.3mm_D2.5mm_P7.62mm_Horizontal,https://www.amazon.com/gp/product/B07HDFSV7C
31,"R32, R33, R34, R35, R36, R37, R38, R39, R40",9,100k,Resistor_THT:R_Axial_DIN0207_L6.3mm_D2.5mm_P7.62mm_Horizontal,https://www.amazon.com/gp/product/B07HDG9K8P
32,"RV1, RV2",2,2k Pot,Potentiometer_THT:Potentiometer_Bourns_3386F_Vertical,https://www.digikey.com/en/products/detail/bourns-inc./3386F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
33,U1,1,TLC555CP,Package_DIP:DIP-8_W7.62mm,https://www.digikey.com/en/products/detail/texas-instruments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
34,U2,1,LM6132BIN/NOPB,Package_DIP:DIP-8_W7.62mm,https://www.digikey.com/en/products/detail/texas-instruments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
35,U3,1,MCP23008-xP,Package_DIP:DIP-18_W7.62mm,https://www.digikey.com/en/products/detail/microchip-technol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
36,"U4, U5, U6, U7, U8",5,SFH617A-1,Package_DIP:DIP-4_W7.62mm,https://www.digikey.com/en/products/detail/vishay-semiconduc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
,,,,,https://www.digikey.com/en/products/detail/te-connectivity-a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
,,,,,https://www.digikey.com/en/products/detail/te-connectivity-a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
